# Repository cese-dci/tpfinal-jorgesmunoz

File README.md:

# Replica Sparkfun VS1053
* Autor: Jorge Salvador Muñoz.
* jorgesmunoz@gmail.com .
* Github: jorgesmunoz .
* tpfinal-jorgesmunoz created by GitHub Classroom .

Replica Sparkfun VS1053 - Vista 3D

Esquematic Kicad

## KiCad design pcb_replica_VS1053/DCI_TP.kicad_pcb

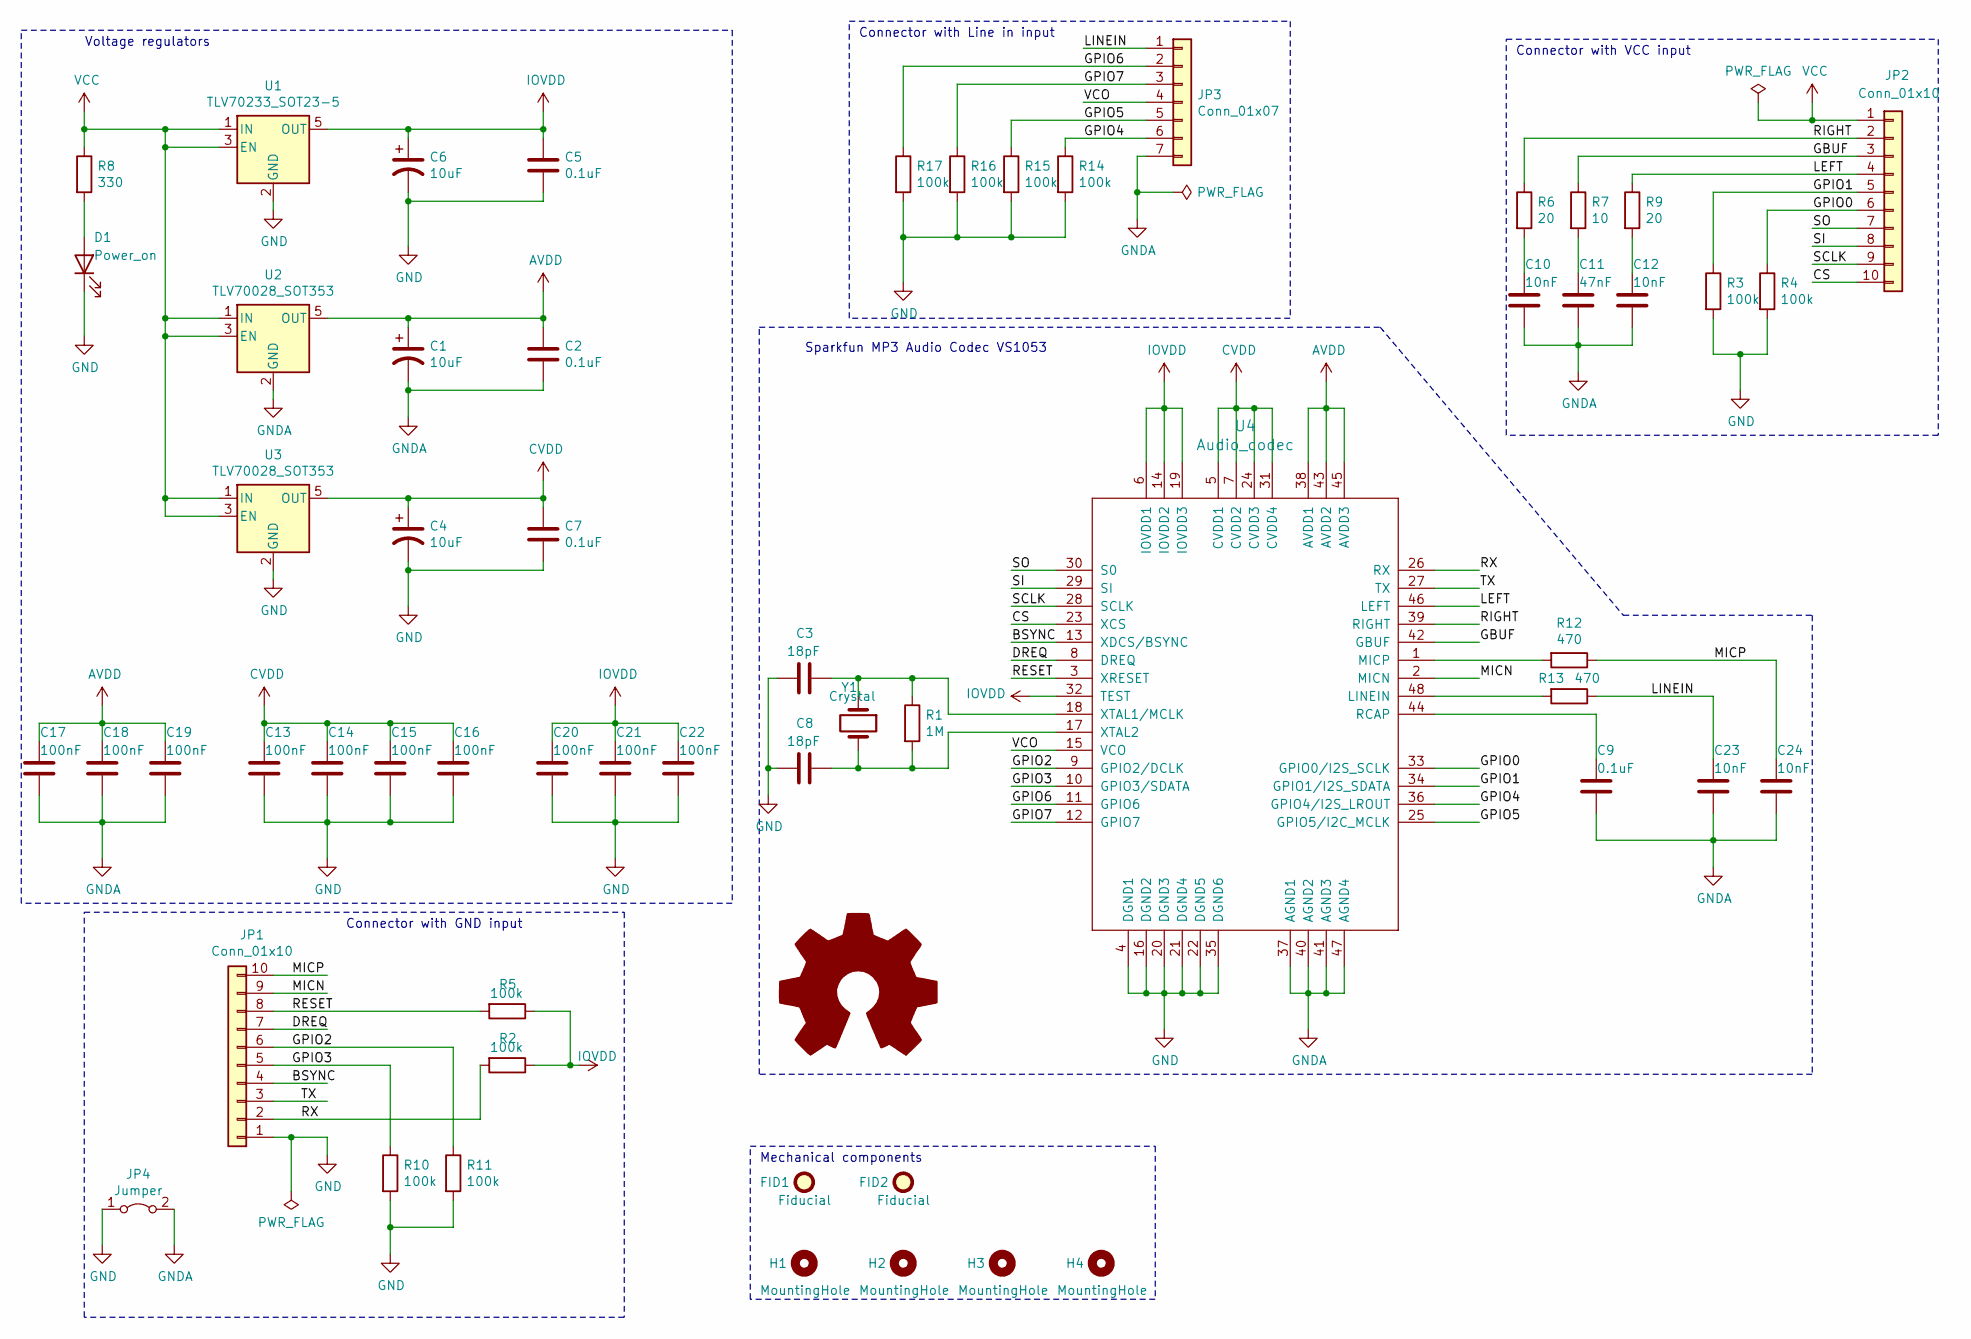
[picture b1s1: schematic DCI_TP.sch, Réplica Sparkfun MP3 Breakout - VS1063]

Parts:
C1, C4, C6: 10uF; C_1206_3216Metric
C2, C5, C7, C9: 0.1uF; C_0805_2012Metric
C3, C8: 18pF; C_0805_2012Metric
C10, C12, C23, C24: 10nF; C_0805_2012Metric
C11: 47nF; C_0805_2012Metric
C13, C14, C15, C16, C17, C18, C19, C20, C21, C22: 100nF; C_0805_2012Metric
D1: Power_on; LED_0805_2012Metric
FID1, FID2: Fiducial; Fiducial_0.5mm_Mask1.5mm
H1, H2, H3, H4: MountingHole; MountingHole_3.2mm_M3_ISO14580
JP1, JP2: Conn_01x10; PinHeader_1x10_P2.54mm_Vertical
JP3: Conn_01x07; PinHeader_1x07_P2.54mm_Vertical
JP4: Jumper; SolderJumper-2_P1.3mm_Bridged_Pad1.0x1.5mm
LOGO1: Logo_Open_Hardware_Large; OSHW-Symbol_6.7x6mm_SilkScreen
R1: 1M; R_0805_2012Metric
R2, R3, R4, R5, R10, R11, R14, R15, R16, R17: 100k; R_0805_2012Metric
R6, R9: 20; R_0805_2012Metric
R7: 10; R_0805_2012Metric
R8: 330; R_0805_2012Metric
R12, R13: 470; R_0805_2012Metric
U1: TLV70233_SOT23-5; SOT-23-5
U2, U3: TLV70028_SOT353; SOT-353_SC-70-5
U4: Audio_codec; LQFP-48_7x7mm_P0.5mm
Y1: Crystal; Oscillator_SMD_EuroQuartz_XO53-4Pin_5.0x3.2mm

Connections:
/BSYNC: JP1.4, U4.13 (XDCS/BSYNC)
/CS: JP2.10, U4.23 (XCS)
/DREQ: JP1.7, U4.8 (DREQ)
/GBUF: JP2.3, R7.1, U4.42 (GBUF)
/GPIO0: JP2.6, R4.1, U4.33 (GPIO0/I2S_SCLK)
/GPIO1: JP2.5, R3.1, U4.34 (GPIO1/I2S_SDATA)
/GPIO2: JP1.6, R11.1, U4.9 (GPIO2/DCLK)
/GPIO3: JP1.5, R10.1, U4.10 (GPIO3/SDATA)
/GPIO4: JP3.6, R14.1, U4.36 (GPIO4/I2S_LROUT)
/GPIO5: JP3.5, R15.1, U4.25 (GPIO5/I2C_MCLK)
/GPIO6: JP3.2, R17.1, U4.11 (GPIO6)
/GPIO7: JP3.3, R16.1, U4.12 (GPIO7)
/LEFT: JP2.4, R9.1, U4.46 (LEFT)
/LINEIN: C23.1, JP3.1, R13.1
/MICN: JP1.9, U4.2 (MICN)
/MICP: C24.1, JP1.10, R12.1
/RESET: JP1.8, R5.2, U4.3 (XRESET)
/RIGHT: JP2.2, R6.1, U4.39 (RIGHT)
/RX: JP1.2, R2.2, U4.26 (RX)
/SCLK: JP2.9, U4.28 (SCLK)
/SI: JP2.8, U4.29 (SI)
/SO: JP2.7, U4.30 (S0)
/TX: JP1.3, U4.27 (TX)
/VCO: JP3.4, U4.15 (VCO)
AVDD: C1.1, C2.1, C17.1, C18.1, C19.1, U2.5 (OUT), U4.38 (AVDD1), U4.43 (AVDD2), U4.45 (AVDD3)
CVDD: C4.1, C7.1, C13.1, C14.1, C15.1, C16.1, U3.5 (OUT), U4.5 (CVDD1), U4.7 (CVDD2), U4.24 (CVDD3), U4.31 (CVDD4)
GND: C3.2, C4.2, C5.2, C6.2, C7.2, C8.2, C13.2, C14.2, C15.2, C16.2, C20.2, C21.2, C22.2, D1.1 (K), JP1.1, JP4.1 (A), R3.2, R4.2, R10.2, R11.2, R14.2, R15.2, R16.2, R17.2, U1.2 (GND), U3.2 (GND), U4.4 (DGND1), U4.16 (DGND2), U4.20 (DGND3), U4.21 (DGND4), U4.22 (DGND5), U4.35 (DGND6)
GNDA: C1.2, C2.2, C9.2, C10.2, C11.2, C12.2, C17.2, C18.2, C19.2, C23.2, C24.2, JP3.7, JP4.2 (B), U2.2 (GND), U4.37 (AGND1), U4.40 (AGND2), U4.41 (AGND3), U4.47 (AGND4)
IOVDD: C5.1, C6.1, C20.1, C21.1, C22.1, R2.1, R5.1, U1.5 (OUT), U4.6 (IOVDD1), U4.14 (IOVDD2), U4.19 (IOVDD3), U4.32 (TEST)
unnamed: C3.1, R1.1, U4.18 (XTAL1/MCLK), Y1.1
unnamed: C8.1, R1.2, U4.17 (XTAL2), Y1.2
unnamed: C9.1, U4.44 (RCAP)
unnamed: C10.1, R6.2
unnamed: C11.1, R7.2
unnamed: C12.1, R9.2
unnamed: D1.2 (A), R8.2
unnamed: R12.2, U4.1 (MICP)
unnamed: R13.2, U4.48 (LINEIN)
VCC: JP2.1, R8.1, U1.1 (IN), U1.3 (EN), U2.1 (IN), U2.3 (EN), U3.1 (IN), U3.3 (EN)

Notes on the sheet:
Mechanical components
Voltage regulators
Connector with VCC input
Connector with GND input
Sparkfun MP3 Audio Codec VS1053
Connector with Line in input

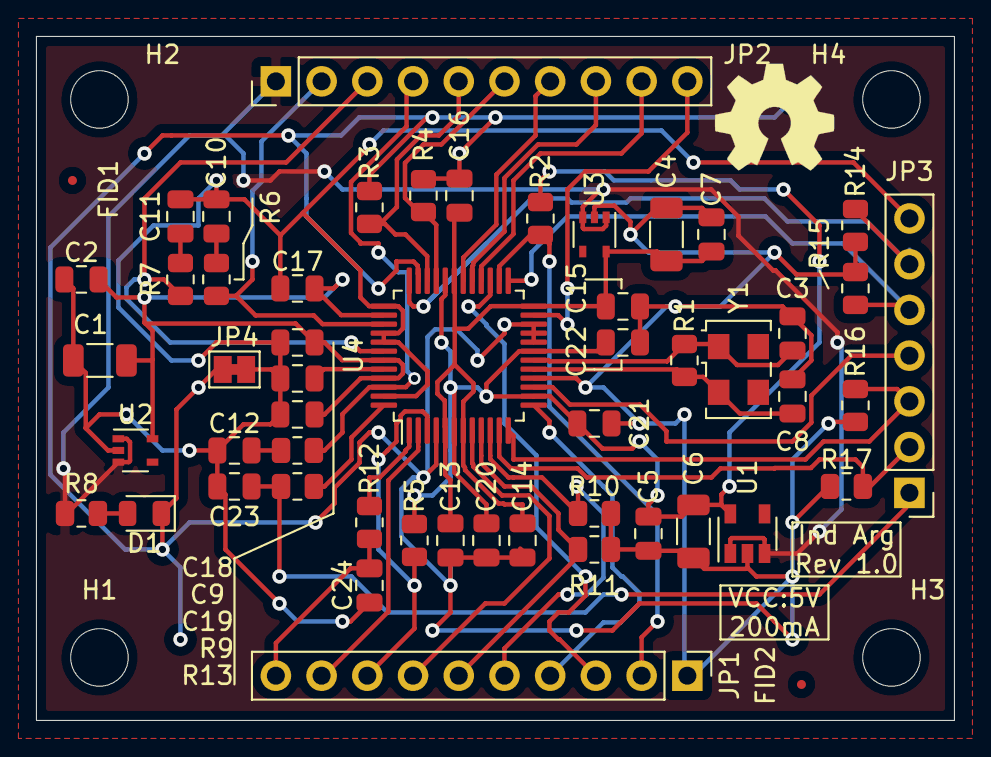
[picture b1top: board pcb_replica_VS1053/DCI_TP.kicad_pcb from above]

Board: 2 copper layers, 51.0 x 38.0 mm, 58 parts (0 on the bottom side), 39 nets.

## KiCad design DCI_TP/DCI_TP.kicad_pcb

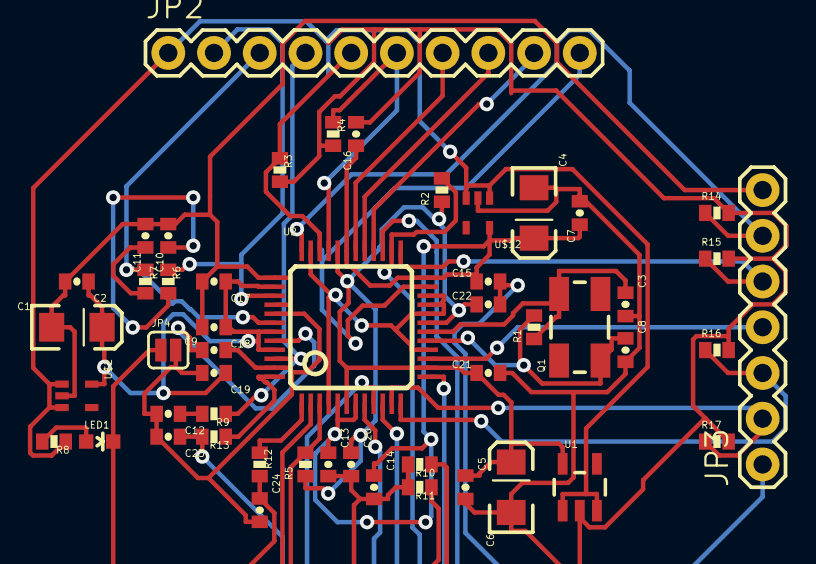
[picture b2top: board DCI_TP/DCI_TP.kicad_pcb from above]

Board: 2 copper layers, 50 parts (0 on the bottom side), 36 nets.

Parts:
C1, C4, C6: 10uF; EIA3216
C2, C5, C7, C9: 0.1uF; 0402-CAP
C3, C8: 18pF; 0402-CAP
C10, C12, C23, C24: 10nF; 0402-CAP
C11: 47nF; 0402-CAP
C13, C14, C15, C16, C17, C18, C19, C20, C21, C22: 100nF; 0402-CAP
JP2: M10; 1X10
JP3: M07; 1X07
JP4: JUMPER; SJ_2S
LED1: Power; LED-0603
Q1: 12.288MHz; CRYSTAL-SMD-5X3
R1: 1M; 0402-RES
R2, R3, R4, R5, R10, R11, R14, R15, R16, R17: 100k; 0402-RES
R6, R9: 20; 0402-RES
R7: 10; 0402-RES
R8: 330; 0402-RES
R12, R13: 470; 0402-RES
U1: 3.3V; SOT23-5
U2: VS1053; LQFP-48
U$2: 2.8V; SC70
U$12: 1.8V; SC70

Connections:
/AGND: C1.C, C2.2, C9.2, C10.2, C11.2, C12.2, C17.2, C18.2, C19.2, C23.2, C24.2, JP3.7, JP4.2, U2.37, U2.40, U2.41, U2.47, U$2.2
/AVDD: C1.A, C2.1, C17.1, C18.1, C19.1, U2.38, U2.43, U2.45, U$2.5
/BSYNC: JP2.4, U2.13
/CVDD: C4.A, C7.1, C13.1, C14.1, C15.1, C16.1, U2.5, U2.7, U2.24, U2.31, U$12.5
/DREQ: JP2.7, U2.8
/GBUF: R7.1, U2.42
/GPIO0: R4.1, U2.33
/GPIO1: R3.1, U2.34
/GPIO2: JP2.6, R11.1, U2.9
/GPIO3: JP2.5, R10.1, U2.10
/GPIO4: JP3.6, R14.1, U2.36
/GPIO5: JP3.5, R15.1, U2.25
/GPIO6: JP3.2, R17.1, U2.11
/GPIO7: JP3.3, R16.1, U2.12
/IOVDD: C5.1, C6.A, C20.1, C21.1, C22.1, R2.1, R5.1, U1.5, U2.6, U2.14, U2.19, U2.32
/LEFT: R9.1, U2.46
/LINEIN: C23.1, JP3.1, R13.2
/MICN: JP2.9, U2.2
/MICP: C24.1, JP2.10, R12.2
/PWR_FLAG: U2.4, U2.16, U2.20, U2.21, U2.22, U2.35
/RESET: JP2.8, R5.2, U2.3
/RIGHT: R6.1, U2.39
/RX: JP2.2, R2.2, U2.26
/TX: JP2.3, U2.27
/VCC: R8.1, U1.1, U1.3, U$2.1, U$2.3, U$12.1, U$12.3
/VCO: JP3.4, U2.15
GND: C3.2, C4.C, C5.2, C6.C, C7.2, C8.2, C13.2, C14.2, C15.2, C16.2, C20.2, C21.2, C22.2, JP2.1, JP4.1, LED1.C, R3.2, R4.2, R10.2, R11.2, R14.2, R15.2, R16.2, R17.2, U1.2, U$12.2
unnamed: C3.1, Q1.3, R1.1, U2.18
unnamed: C8.1, Q1.1, R1.2, U2.17
unnamed: C9.1, U2.44
unnamed: C10.1, R6.2
unnamed: C11.1, R7.2
unnamed: C12.1, R9.2
unnamed: LED1.A, R8.2
unnamed: R12.1, U2.1
unnamed: R13.1, U2.48

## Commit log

2020-10-10 Commit TP DCI
    Se sube esquemático y primeros avances del PCB.
2020-11-04 New commit DCI
    Se suben avances de PCB
2020-11-15 Test
2020-11-15 Version final TP DCI
2020-11-15 Actualizacion TP

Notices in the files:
pcb_replica_VS1053/DCI_TP.kicad_pcb:
Creative Commons ShareAlike 4.0 International
